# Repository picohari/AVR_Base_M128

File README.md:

# AVR ATmega128 development board

Simple board with ATmega128 microcontroller and breakout connectors for each port

## Hardware:

* Each port is accessible over Molex 10pin header (Px0 - Px7, +5V, GND)
* L7805 voltage regulator
* Serial driver ic for 2x RS-232
* LCD connector for HD44780 displays (no BUSY reading possible, just wait..)
* Pinheader for display background LED
* Reset button
* 16 MHz crystal oscillator
* Additional +5V and GND pins
* Holes for easy mounting

## Software:

Check out my other GitHub pages for more driver support (only C), I will post some libraries once I've got more time...

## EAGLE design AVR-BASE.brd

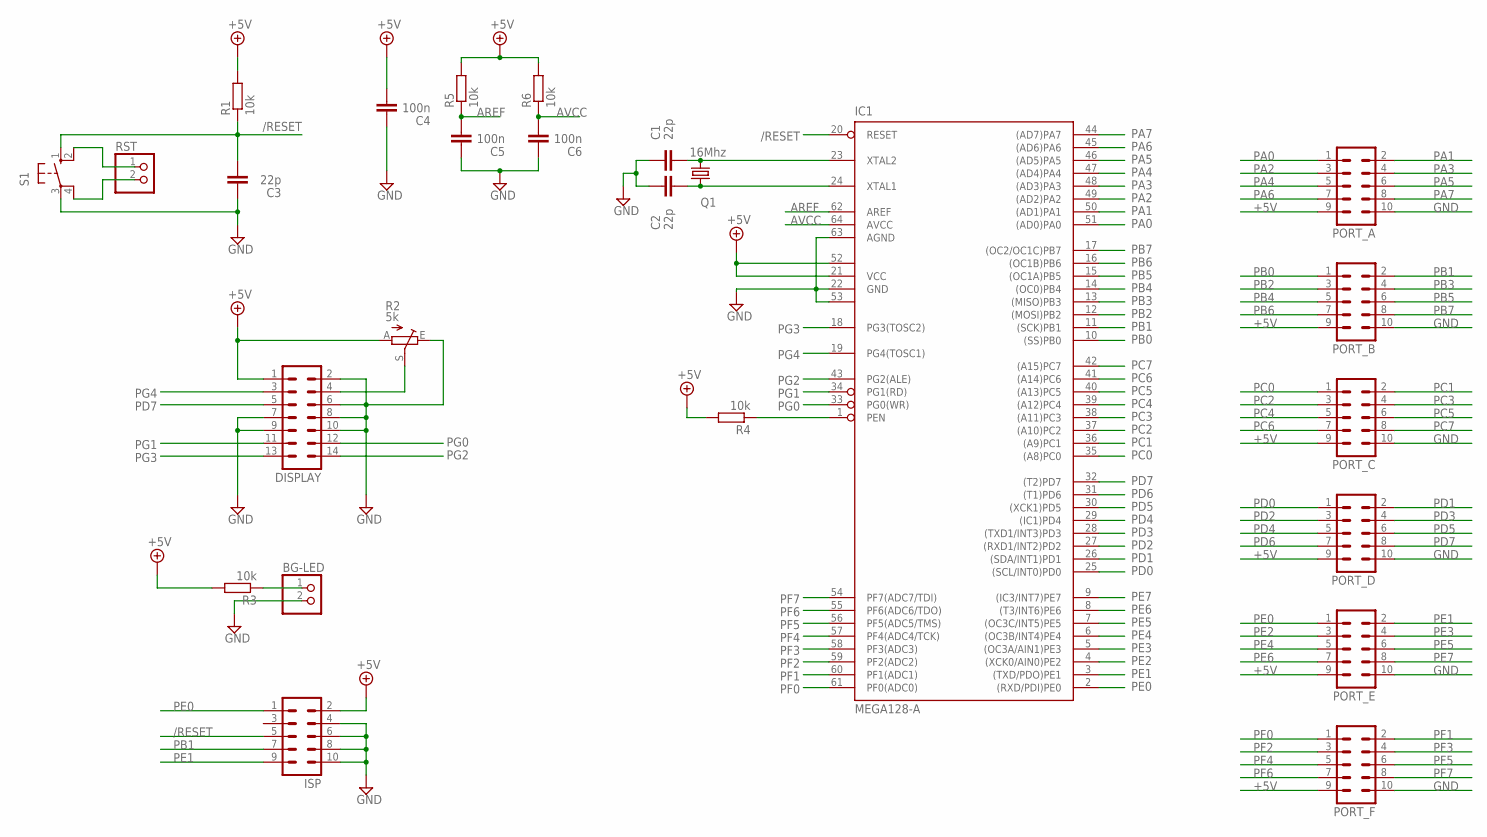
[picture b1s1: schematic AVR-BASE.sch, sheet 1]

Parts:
BG-LED: PINHD-1X2; 1X02
C1, C2, C3: 22p; C025-025X050
C4, C5, C6: 100n; C025-025X050
DISPLAY: ML14
IC1: MEGA128-A; TQFP64
ISP: ML10
PORT_A: ML10
PORT_B: ML10
PORT_C: ML10
PORT_D: ML10
PORT_E: ML10
PORT_F: ML10
Q1: 16Mhz; HC49U-V
R1, R3: 10k; 0207/7
R2: 5k; B25P
R4, R5, R6: 10k; 0204/5
RST: PINHD-1X2; 1X02
S1: 10-XX; B3F-10XX

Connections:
+5V: C4.2, DISPLAY.1, IC1.21 (VCC), IC1.52 (VCC1), ISP.2, PORT_A.9, PORT_B.9, PORT_C.9, PORT_D.9, PORT_E.9, PORT_F.9, R1.2, R2.A, R3.2, R4.2, R5.2, R6.2; also elsewhere on the board
/RESET: C3.2, IC1.20 (RESET), ISP.5, R1.1, S1.1 (S)
AREF: C5.2, IC1.62 (AREF), R5.1
AVCC: C6.2, IC1.64 (AVCC), R6.1
GND: BG-LED.2, C1.1, C2.1, C3.1, C4.1, C5.1, C6.1, DISPLAY.2, DISPLAY.6, DISPLAY.7, DISPLAY.8, DISPLAY.9, DISPLAY.10, IC1.22 (GND), IC1.53 (GND1), IC1.63 (AGND), ISP.4, ISP.6, ISP.8, ISP.10, PORT_A.10, PORT_B.10, PORT_C.10, PORT_D.10, PORT_E.10, PORT_F.10, R2.E, S1.3; also elsewhere on the board
unnamed: C1.2, IC1.23 (XTAL2), Q1.2
unnamed: C2.2, IC1.24 (XTAL1), Q1.1
unnamed: RST.1, S1.2 (S1)
unnamed: DISPLAY.4, R2.S
unnamed: RST.2, S1.4 (P1)
unnamed: IC1.1 (PEN), R4.1
unnamed: BG-LED.1, R3.1
PA0: IC1.51 ((AD0)PA0), PORT_A.1
PA1: IC1.50 ((AD1)PA1), PORT_A.2
PA2: IC1.49 ((AD2)PA2), PORT_A.3
PA3: IC1.48 ((AD3)PA3), PORT_A.4
PA4: IC1.47 ((AD4)PA4), PORT_A.5
PA5: IC1.46 ((AD5)PA5), PORT_A.6
PA6: IC1.45 ((AD6)PA6), PORT_A.7
PA7: IC1.44 ((AD7)PA7), PORT_A.8
PB0: IC1.10 ((SS)PB0), PORT_B.1
PB1: IC1.11 ((SCK)PB1), ISP.7, PORT_B.2
PB2: IC1.12 ((MOSI)PB2), PORT_B.3
PB3: IC1.13 ((MISO)PB3), PORT_B.4
PB4: IC1.14 ((OC0)PB4), PORT_B.5
PB5: IC1.15 ((OC1A)PB5), PORT_B.6
PB6: IC1.16 ((OC1B)PB6), PORT_B.7
PB7: IC1.17 ((OC2/OC1C)PB7), PORT_B.8
PC0: IC1.35 ((A8)PC0), PORT_C.1
PC1: IC1.36 ((A9)PC1), PORT_C.2
PC2: IC1.37 ((A10)PC2), PORT_C.3
PC3: IC1.38 ((A11)PC3), PORT_C.4
PC4: IC1.39 ((A12)PC4), PORT_C.5
PC5: IC1.40 ((A13)PC5), PORT_C.6
PC6: IC1.41 ((A14)PC6), PORT_C.7
PC7: IC1.42 ((A15)PC7), PORT_C.8
PD0: IC1.25 ((SCL/INT0)PD0), PORT_D.1
PD1: IC1.26 ((SDA/INT1)PD1), PORT_D.2
PD2: IC1.27 ((RXD1/INT2)PD2), PORT_D.3; also elsewhere on the board
PD3: IC1.28 ((TXD1/INT3)PD3), PORT_D.4; also elsewhere on the board
PD4: IC1.29 ((IC1)PD4), PORT_D.5
PD5: IC1.30 ((XCK1)PD5), PORT_D.6
PD6: IC1.31 ((T1)PD6), PORT_D.7
PD7: DISPLAY.5, IC1.32 ((T2)PD7), PORT_D.8
PE0: IC1.2 ((RXD/PDI)PE0), ISP.1, PORT_E.1; also elsewhere on the board
PE1: IC1.3 ((TXD/PDO)PE1), ISP.9, PORT_E.2; also elsewhere on the board
PE2: IC1.4 ((XCK0/AIN0)PE2), PORT_E.3
PE3: IC1.5 ((OC3A/AIN1)PE3), PORT_E.4
PE4: IC1.6 ((OC3B/INT4)PE4), PORT_E.5
PE5: IC1.7 ((OC3C/INT5)PE5), PORT_E.6
PE6: IC1.8 ((T3/INT6)PE6), PORT_E.7
PE7: IC1.9 ((IC3/INT7)PE7), PORT_E.8
PF0: IC1.61 (PF0(ADC0)), PORT_F.1
PF1: IC1.60 (PF1(ADC1)), PORT_F.2
PF2: IC1.59 (PF2(ADC2)), PORT_F.3
PF3: IC1.58 (PF3(ADC3)), PORT_F.4
PF4: IC1.57 (PF4(ADC4/TCK)), PORT_F.5
PF5: IC1.56 (PF5(ADC5/TMS)), PORT_F.6
PF6: IC1.55 (PF6(ADC6/TDO)), PORT_F.7
PF7: IC1.54 (PF7(ADC7/TDI)), PORT_F.8
PG0: DISPLAY.12, IC1.33 (PG0(WR))
PG1: DISPLAY.11, IC1.34 (PG1(RD))
PG2: DISPLAY.14, IC1.43 (PG2(ALE))
PG3: DISPLAY.13, IC1.18 (PG3(TOSC2))
PG4: DISPLAY.3, IC1.19 (PG4(TOSC1))

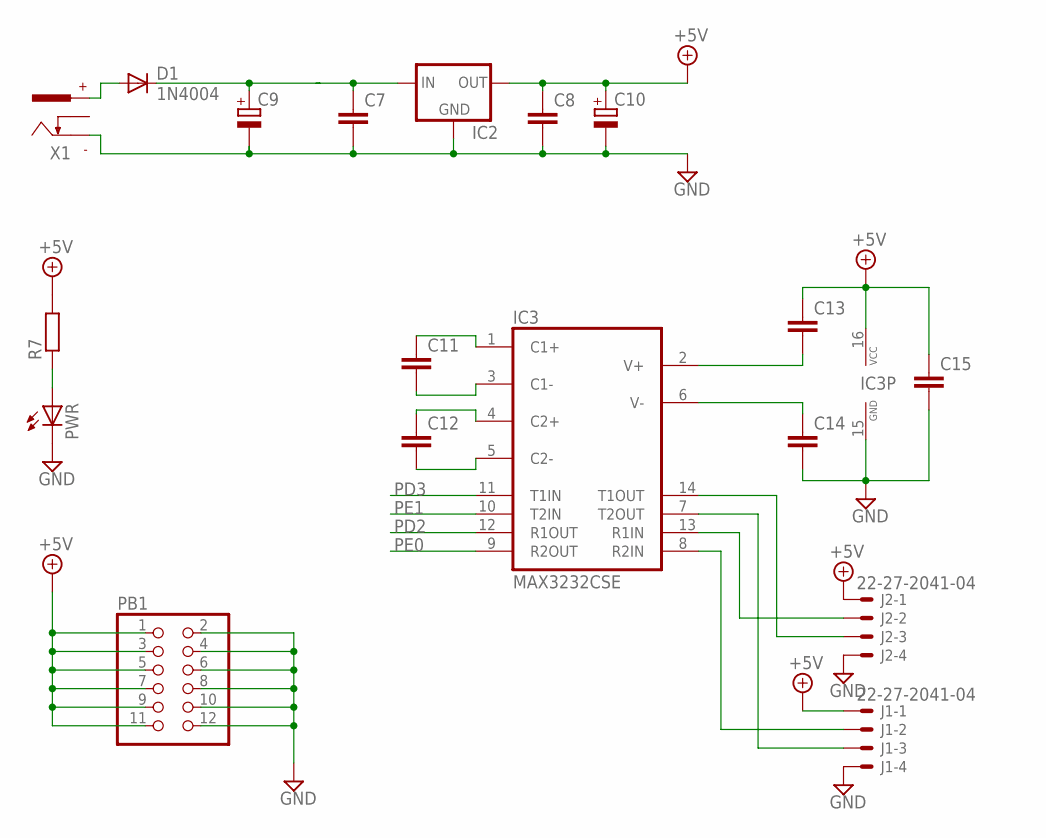
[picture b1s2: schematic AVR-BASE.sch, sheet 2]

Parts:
C7, C8, C11, C12, C13, C14, C15: C-EU025-025X050; C025-025X050
C9, C10: CPOL-EUE3.5-8; E3,5-8
D1: 1N4004; DO41-10
IC2: 78XXL
IC3: MAX3232CSE; SO16
J1, J2: 22-27-2041-04; 6410-04
PB1: PINHD-2X6; 2X06
PWR: LED3MM
R7: R-EU_0204/5; 0204/5
X1: 737992-55; 737992-5

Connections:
+5V: C8.1, C10.+, C13.1, C15.1, IC2.OUT, IC3.16 (VCC), J1.1, J2.1, PB1.1, PB1.3, PB1.5, PB1.7, PB1.9, PB1.11, R7.2; also elsewhere on the board
GND: C7.2, C8.2, C9.-, C10.-, C14.2, C15.2, IC2.GND, IC3.15 (GND), J1.4, J2.4, PB1.2, PB1.4, PB1.6, PB1.8, PB1.10, PB1.12, PWR.K (C), X1.+; also elsewhere on the board
unnamed: C7.1, C9.+, D1.C, IC2.IN
unnamed: D1.A, X1.-1
unnamed: PWR.A, R7.1
unnamed: C11.1, IC3.1 (C1+)
unnamed: C11.2, IC3.3 (C1-)
unnamed: C12.1, IC3.4 (C2+)
unnamed: C12.2, IC3.5 (C2-)
unnamed: C13.2, IC3.2 (V+)
unnamed: C14.1, IC3.6 (V-)
PD2: IC3.12 (R1OUT); also elsewhere on the board
PD3: IC3.11 (T1IN); also elsewhere on the board
PE0: IC3.9 (R2OUT); also elsewhere on the board
PE1: IC3.10 (T2IN); also elsewhere on the board
RX0: IC3.8 (R2IN), J1.2
RX1: IC3.13 (R1IN), J2.2
TX0: IC3.7 (T2OUT), J1.3
TX1: IC3.14 (T1OUT), J2.3

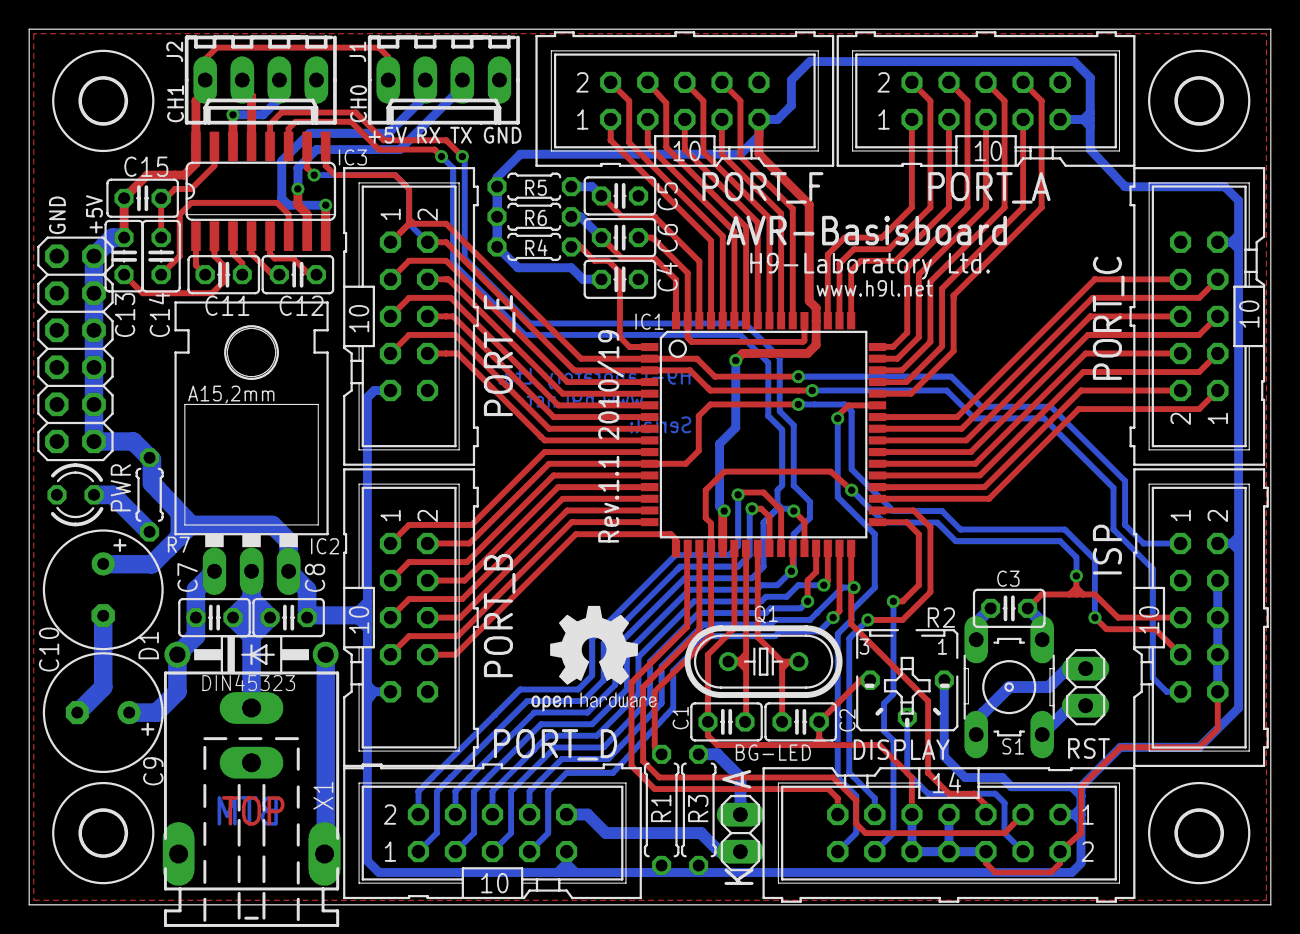
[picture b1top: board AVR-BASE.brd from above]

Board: 2 copper layers, 85.1 x 60.0 mm, 47 parts (0 on the bottom side), 78 nets.

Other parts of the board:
U$1, U$2, U$3, U$4: 3,0

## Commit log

2019-07-15 Added README.md
2019-07-15 Added images folder
2019-07-15 Replaced image
2019-07-15 Corrected image path
